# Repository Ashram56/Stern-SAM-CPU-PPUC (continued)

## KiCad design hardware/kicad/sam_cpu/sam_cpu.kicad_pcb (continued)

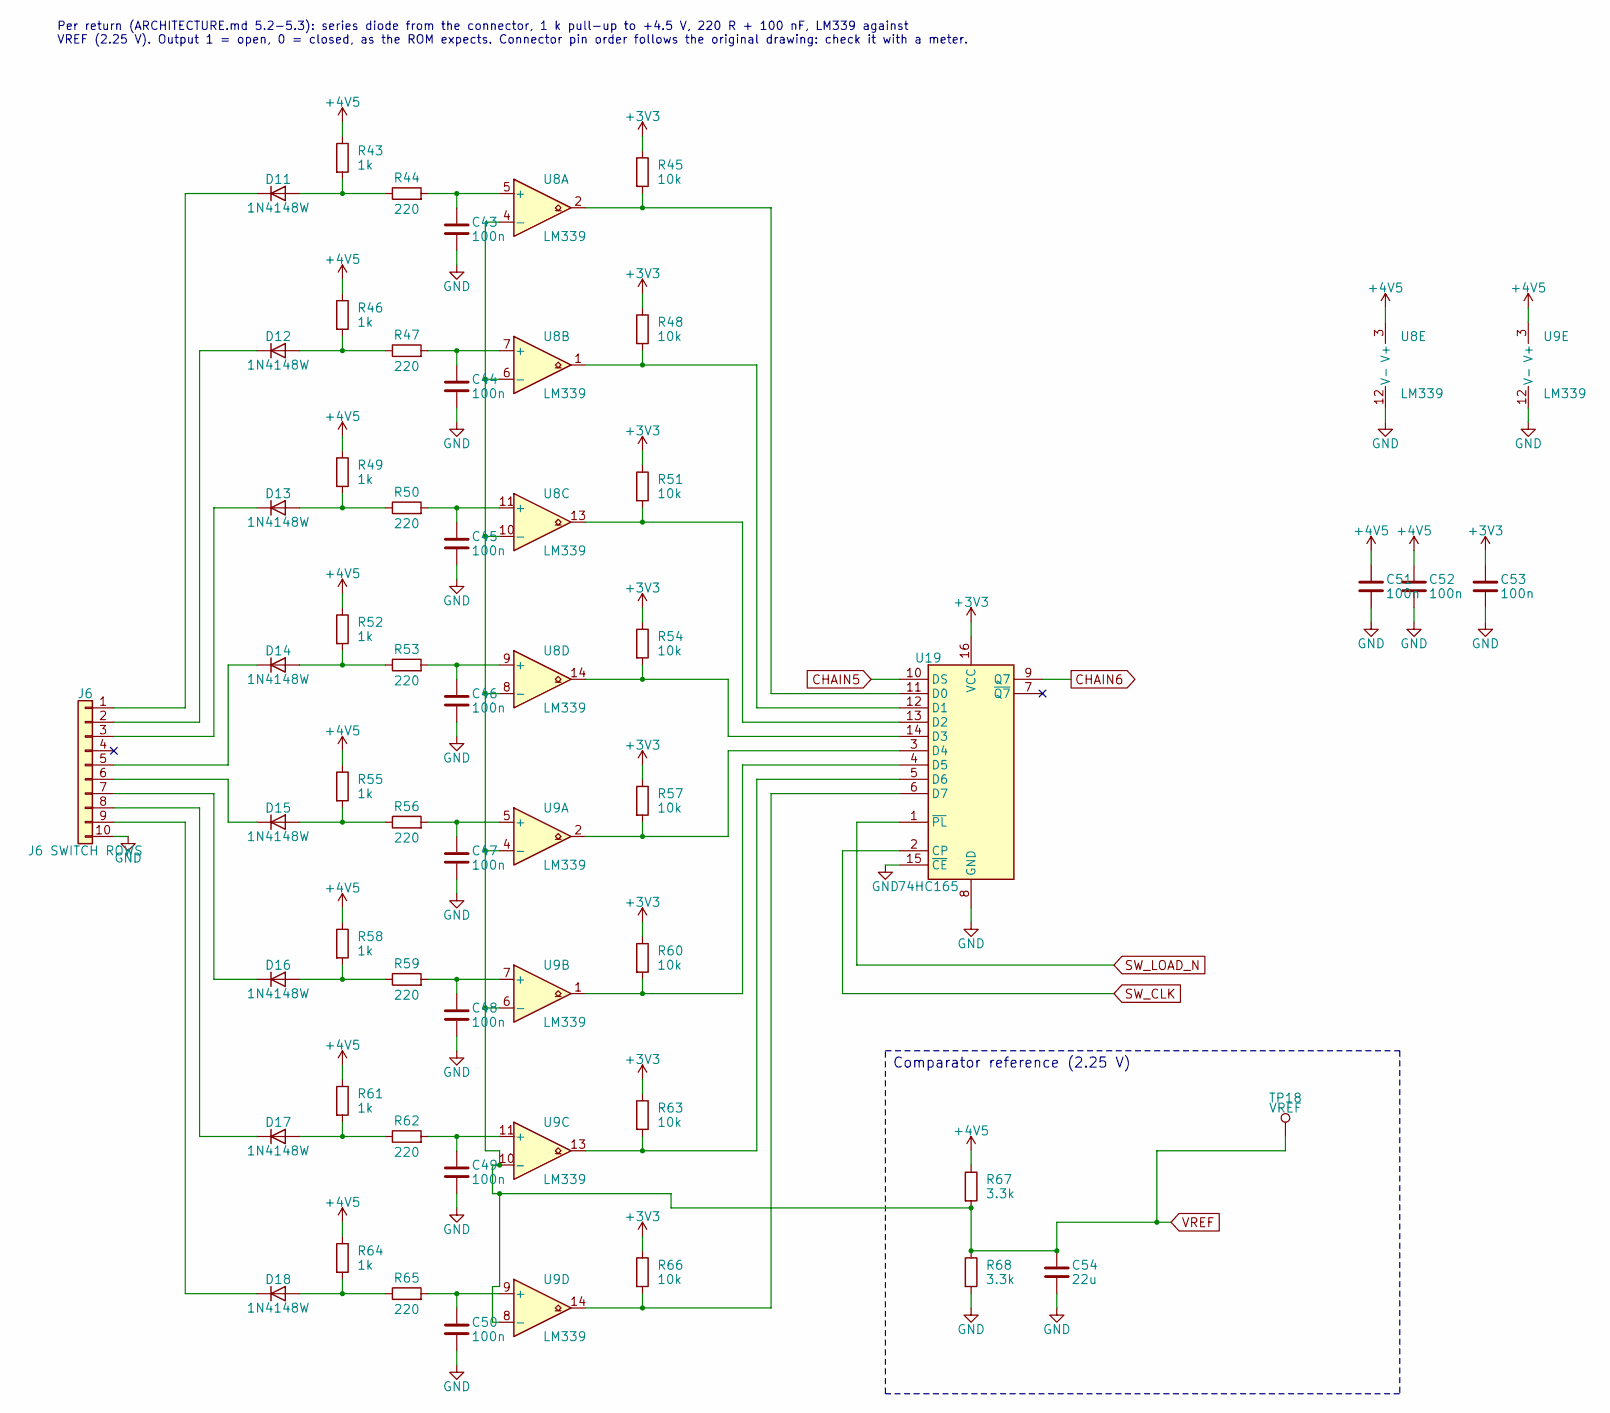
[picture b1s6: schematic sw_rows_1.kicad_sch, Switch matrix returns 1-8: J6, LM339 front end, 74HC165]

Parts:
C43, C44, C45, C46, C47, C48, C49, C50: 100n; C_0603_1608Metric
C51, C52, C53: 100n; C_0805_2012Metric
C54: 22u; C_0805_2012Metric
D11, D12, D13, D14, D15, D16, D17, D18: 1N4148W; D_SOD-123
J6: J6 SWITCH ROWS; Molex_KK-396_A-41791-0010_1x10_P3.96mm_Vertical
R43, R46, R49, R52, R55, R58, R61, R64: 1k; R_0603_1608Metric
R44, R50, R62, R65: 220; R_0805_2012Metric
R45, R51, R57, R60, R63: 10k; R_0603_1608Metric
R47, R53, R56, R59: 220; R_0603_1608Metric
R48, R54, R66: 10k; R_0805_2012Metric
R67: 3.3k; R_0603_1608Metric
R68: 3.3k; R_0805_2012Metric
TP18: VREF; TestPoint_Pad_D1.5mm
U8, U9: LM339; SOIC-14_3.9x8.7mm_P1.27mm
U19: 74HC165; SOIC-16_3.9x9.9mm_P1.27mm

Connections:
+3V3: C53.1, R45.1, R48.1, R51.1, R54.1, R57.1, R60.1, R63.1, R66.1, U19.16 (VCC); also elsewhere on the board
+4V5: C51.1, C52.1, R43.1, R46.1, R49.1, R52.1, R55.1, R58.1, R61.1, R64.1, R67.1, U8.3 (V+), U9.3 (V+); also elsewhere on the board
CHAIN5: U19.10 (DS); also elsewhere on the board
CHAIN6: U19.9 (Q7); also elsewhere on the board
GND: C43.2, C44.2, C45.2, C46.2, C47.2, C48.2, C49.2, C50.2, C51.2, C52.2, C53.2, C54.2, J6.10, R68.2, U8.12 (V-), U9.12 (V-), U19.8 (GND), U19.15 (~CE); also elsewhere on the board
unnamed: D11.2 (A), R43.2, R44.1
unnamed: D11.1 (K), J6.1
unnamed: D12.2 (A), R46.2, R47.1
unnamed: D12.1 (K), J6.2
unnamed: D13.2 (A), R49.2, R50.1
unnamed: D13.1 (K), J6.3
unnamed: D14.2 (A), R52.2, R53.1
unnamed: D14.1 (K), J6.5
unnamed: D15.2 (A), R55.2, R56.1
unnamed: D15.1 (K), J6.6
unnamed: D16.2 (A), R58.2, R59.1
unnamed: D16.1 (K), J6.7
unnamed: D17.2 (A), R61.2, R62.1
unnamed: D17.1 (K), J6.8
unnamed: D18.2 (A), R64.2, R65.1
unnamed: D18.1 (K), J6.9
unnamed: C43.1, R44.2, U8.5 (+)
unnamed: C44.1, R47.2, U8.7 (+)
unnamed: C45.1, R50.2, U8.11 (+)
unnamed: C46.1, R53.2, U8.9 (+)
unnamed: C47.1, R56.2, U9.5 (+)
unnamed: C48.1, R59.2, U9.7 (+)
unnamed: C49.1, R62.2, U9.11 (+)
unnamed: C50.1, R65.2, U9.9 (+)
unnamed: R45.2, U8.2, U19.11 (D0)
unnamed: R48.2, U8.1, U19.12 (D1)
unnamed: R51.2, U8.13, U19.13 (D2)
unnamed: R54.2, U8.14, U19.14 (D3)
unnamed: R57.2, U9.2, U19.3 (D4)
unnamed: R60.2, U9.1, U19.4 (D5)
unnamed: R63.2, U9.13, U19.5 (D6)
unnamed: R66.2, U9.14, U19.6 (D7)
SW_CLK: U19.2 (CP); also elsewhere on the board
SW_LOAD_N: U19.1 (~PL); also elsewhere on the board
VREF: C54.1, R67.2, R68.1, TP18.1, U8.4 (-), U8.6 (-), U8.8 (-), U8.10 (-), U9.4 (-), U9.6 (-), U9.8 (-), U9.10 (-); also elsewhere on the board

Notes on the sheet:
Comparator reference (2.25 V)
Per return (ARCHITECTURE.md 5.2-5.3): series diode from the connector, 1 k pull-up to +4.5 V, 220 R + 100 nF, LM339 against VREF (2.25 V). Output 1 = open, 0 = closed, as the ROM expects. Connector pin order follows the original drawing: check it with a meter.

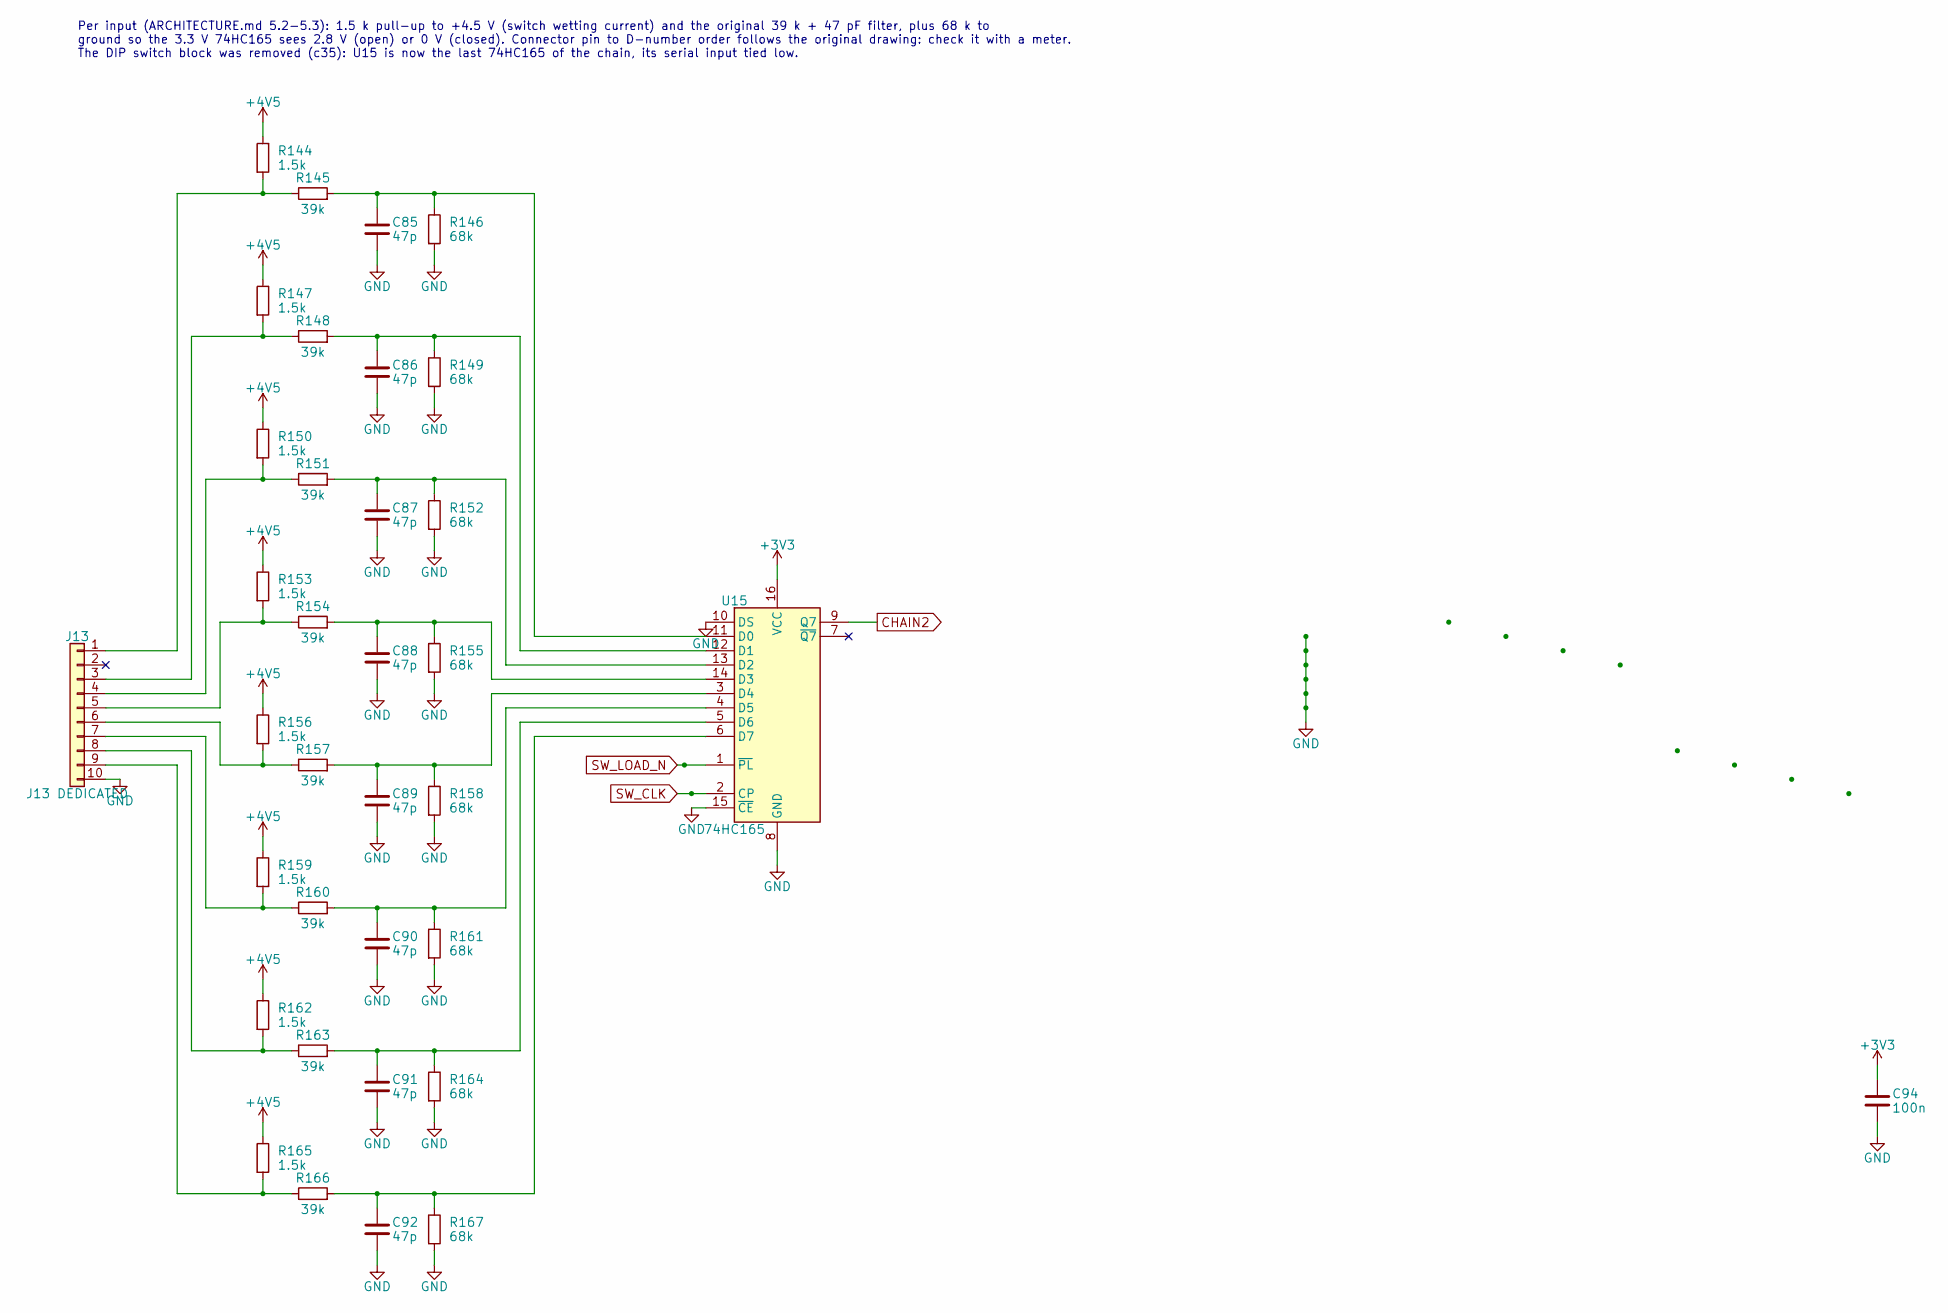
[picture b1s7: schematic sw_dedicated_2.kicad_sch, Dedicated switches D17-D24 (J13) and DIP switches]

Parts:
C85: 47p; C_0805_2012Metric
C86, C87, C88, C89, C90, C91, C92: 47p; C_0603_1608Metric
C94: 100n; C_0805_2012Metric
J13: J13 DEDICATED; Molex_KK-396_A-41791-0010_1x10_P3.96mm_Vertical
R144, R147, R150, R153, R156, R159, R165: 1.5k; R_0603_1608Metric
R145, R148, R151, R154, R157, R160, R163, R166: 39k; R_0603_1608Metric
R146, R149, R152, R161, R167: 68k; R_0603_1608Metric
R155, R158, R164: 68k; R_0805_2012Metric
R162: 1.5k; R_0805_2012Metric
U15: 74HC165; SOIC-16_3.9x9.9mm_P1.27mm

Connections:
+3V3: C94.1, U15.16 (VCC); also elsewhere on the board
+4V5: R144.1, R147.1, R150.1, R153.1, R156.1, R159.1, R162.1, R165.1; also elsewhere on the board
CHAIN2: U15.9 (Q7); also elsewhere on the board
GND: C85.2, C86.2, C87.2, C88.2, C89.2, C90.2, C91.2, C92.2, C94.2, J13.10, R146.2, R149.2, R152.2, R155.2, R158.2, R161.2, R164.2, R167.2, U15.8 (GND), U15.10 (DS), U15.15 (~CE); also elsewhere on the board
unnamed: J13.1, R144.2, R145.1
unnamed: J13.3, R147.2, R148.1
unnamed: J13.4, R150.2, R151.1
unnamed: J13.5, R153.2, R154.1
unnamed: J13.6, R156.2, R157.1
unnamed: J13.7, R159.2, R160.1
unnamed: J13.8, R162.2, R163.1
unnamed: J13.9, R165.2, R166.1
unnamed: C85.1, R145.2, R146.1, U15.11 (D0)
unnamed: C86.1, R148.2, R149.1, U15.12 (D1)
unnamed: C87.1, R151.2, R152.1, U15.13 (D2)
unnamed: C88.1, R154.2, R155.1, U15.14 (D3)
unnamed: C89.1, R157.2, R158.1, U15.3 (D4)
unnamed: C90.1, R160.2, R161.1, U15.4 (D5)
unnamed: C91.1, R163.2, R164.1, U15.5 (D6)
unnamed: C92.1, R166.2, R167.1, U15.6 (D7)
SW_CLK: U15.2 (CP); also elsewhere on the board
SW_LOAD_N: U15.1 (~PL); also elsewhere on the board

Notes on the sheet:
Per input (ARCHITECTURE.md 5.2-5.3): 1.5 k pull-up to +4.5 V (switch wetting current) and the original 39 k + 47 pF filter, plus 68 k to ground so the 3.3 V 74HC165 sees 2.8 V (open) or 0 V (closed). Connector pin to D-number order follows the original drawing: check it with a meter. The DIP switch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

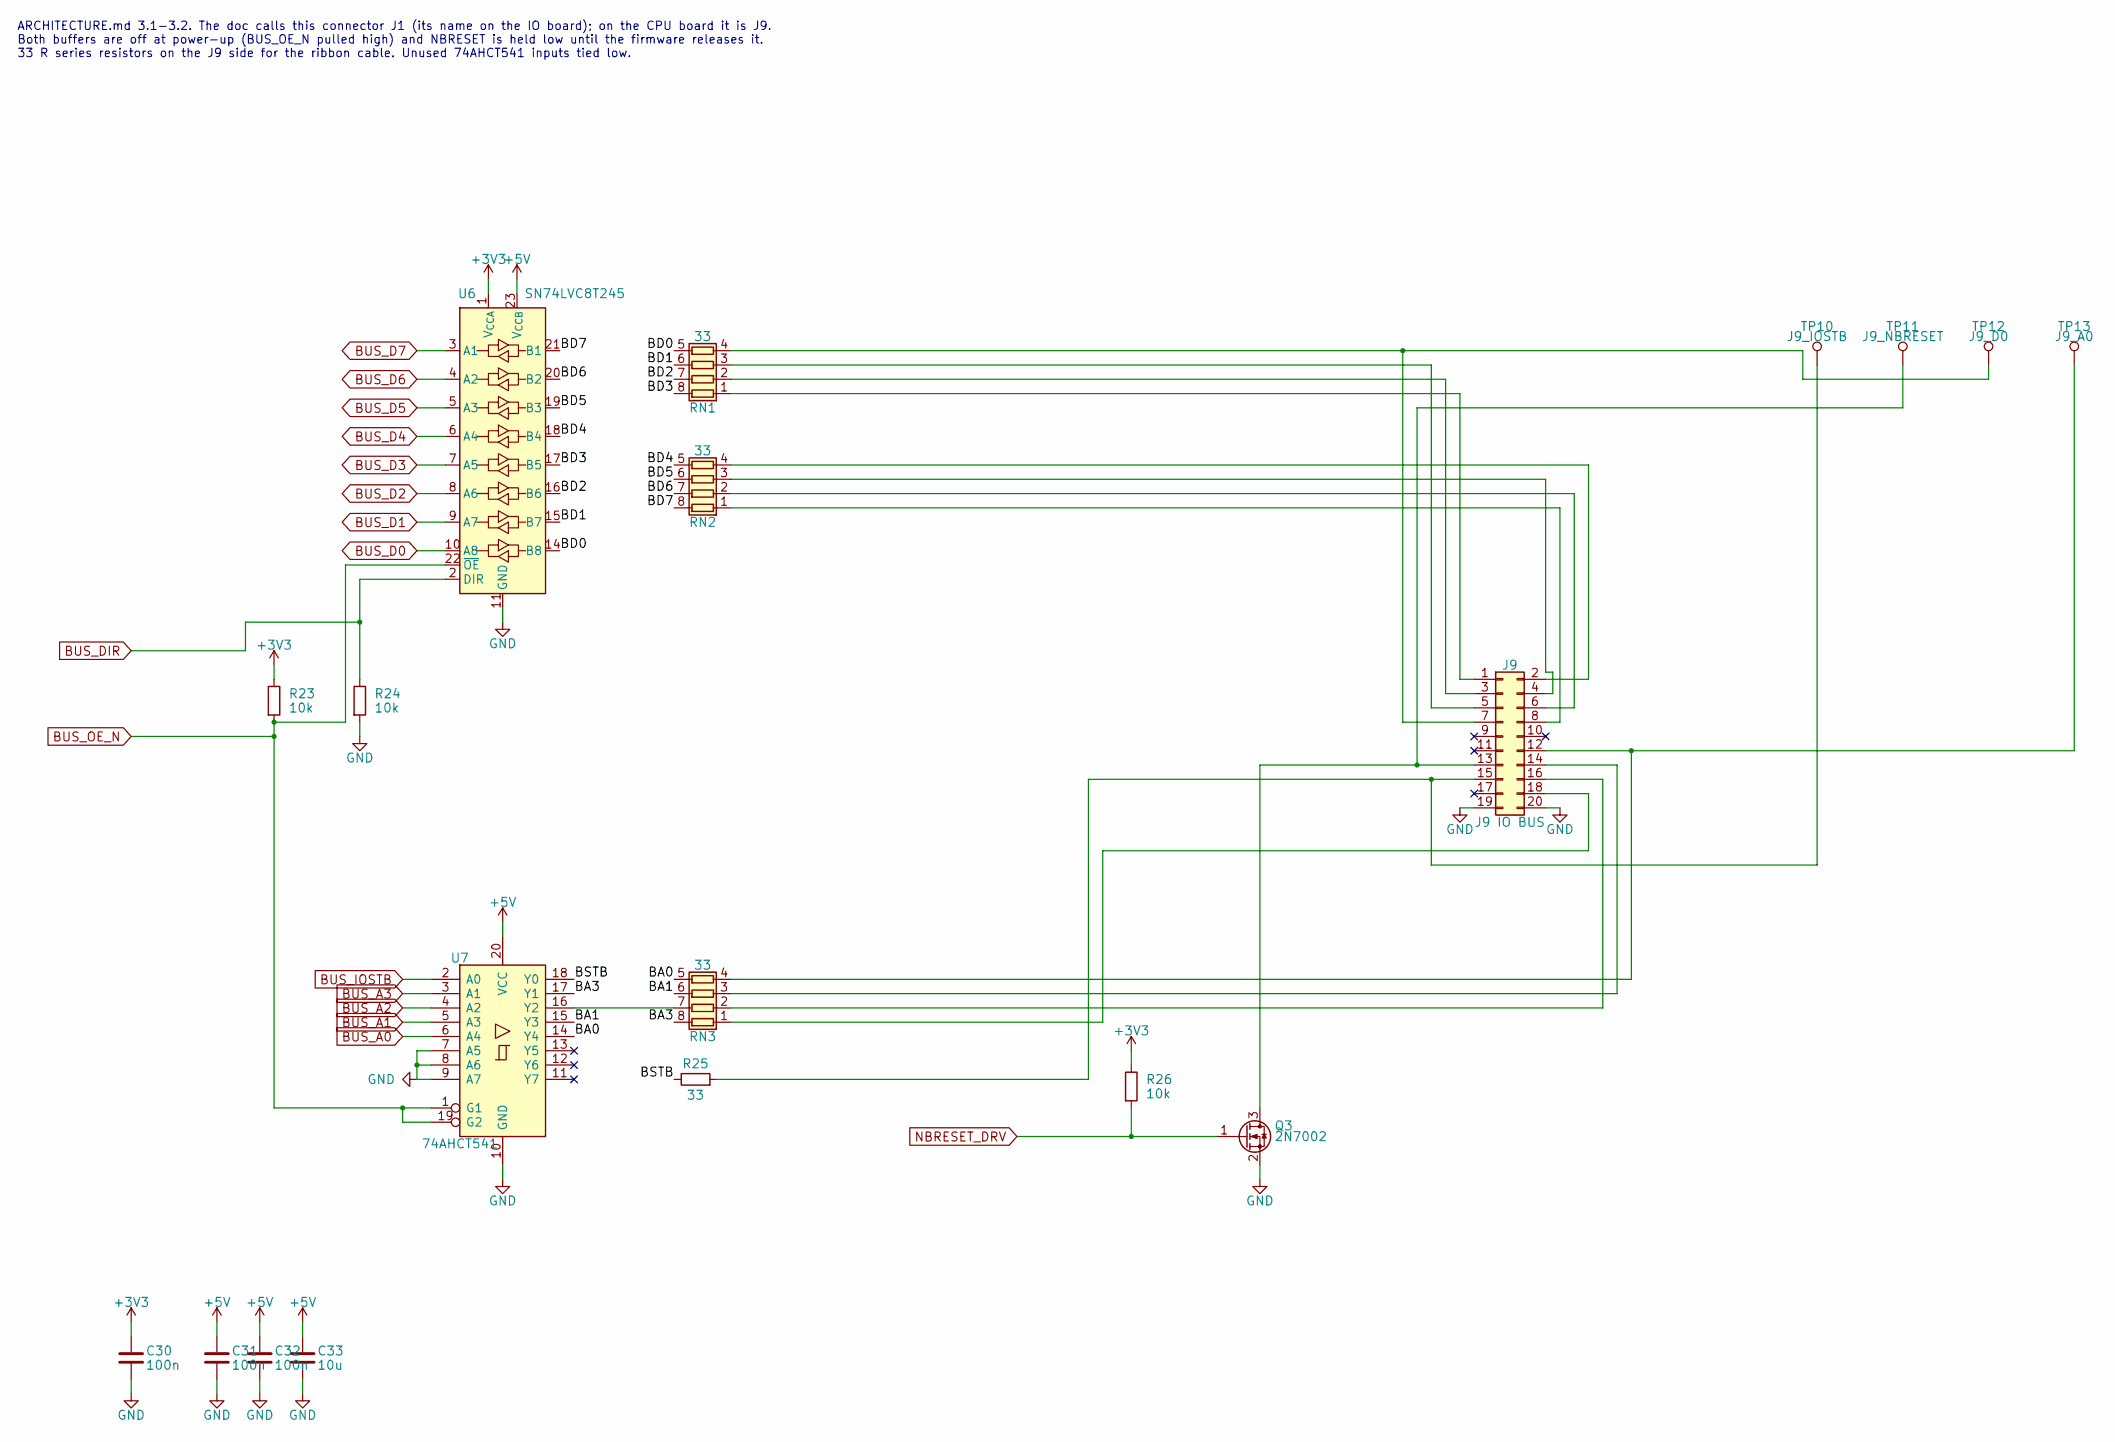
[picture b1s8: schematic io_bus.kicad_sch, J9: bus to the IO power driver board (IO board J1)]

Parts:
C30: 100n; C_0805_2012Metric
C31, C32: 100n; C_0603_1608Metric
C33: 10u; C_0805_2012Metric
J9: J9 IO BUS; IDC-Header_2x10_P2.54mm_Vertical
Q3: 2N7002; SOT-23
R23, R24, R26: 10k; R_0603_1608Metric
R25: 33; R_0603_1608Metric
RN1, RN2, RN3: 33; R_Array_Convex_4x0603
TP10: J9_IOSTB; TestPoint_Pad_D1.5mm
TP11: J9_NBRESET; TestPoint_Pad_D1.5mm
TP12: J9_D0; TestPoint_Pad_D1.5mm
TP13: J9_A0; TestPoint_Pad_D1.5mm
U6: SN74LVC8T245; TSSOP-24_4.4x7.8mm_P0.65mm
U7: 74AHCT541; TSSOP-20_4.4x6.5mm_P0.65mm

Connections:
+3V3: C30.1, R23.1, R26.1, U6.1 (V_{CCA}); also elsewhere on the board
+5V: C31.1, C32.1, C33.1, U6.23 (V_{CCB}), U6.24 (V_{CCB}), U7.20 (VCC); also elsewhere on the board
/IO bus/BA0: RN3.5 (R4.2), U7.14 (Y4)
/IO bus/BA1: RN3.6 (R3.2), U7.15 (Y3)
/IO bus/BA3: RN3.8 (R1.2), U7.17 (Y1)
/IO bus/BD0: RN1.5 (R4.2), U6.14 (B8)
/IO bus/BD1: RN1.6 (R3.2), U6.15 (B7)
/IO bus/BD2: RN1.7 (R2.2), U6.16 (B6)
/IO bus/BD3: RN1.8 (R1.2), U6.17 (B5)
/IO bus/BD4: RN2.5 (R4.2), U6.18 (B4)
/IO bus/BD5: RN2.6 (R3.2), U6.19 (B3)
/IO bus/BD6: RN2.7 (R2.2), U6.20 (B2)
/IO bus/BD7: RN2.8 (R1.2), U6.21 (B1)
/IO bus/BSTB: R25.1, U7.18 (Y0)
BUS_A0: U7.6 (A4); also elsewhere on the board
BUS_A1: U7.5 (A3); also elsewhere on the board
BUS_A2: U7.4 (A2); also elsewhere on the board
BUS_A3: U7.3 (A1); also elsewhere on the board
BUS_D0: U6.10 (A8); also elsewhere on the board
BUS_D1: U6.9 (A7); also elsewhere on the board
BUS_D2: U6.8 (A6); also elsewhere on the board
BUS_D3: U6.7 (A5); also elsewhere on the board
BUS_D4: U6.6 (A4); also elsewhere on the board
BUS_D5: U6.5 (A3); also elsewhere on the board
BUS_D6: U6.4 (A2); also elsewhere on the board
BUS_D7: U6.3 (A1); also elsewhere on the board
BUS_DIR: R24.1, U6.2 (DIR); also elsewhere on the board
BUS_IOSTB: U7.2 (A0); also elsewhere on the board
BUS_OE_N: R23.2, U6.22 (~OE), U7.1 (G1), U7.19 (G2); also elsewhere on the board
GND: C30.2, C31.2, C32.2, C33.2, J9.19, J9.20, Q3.2 (S), R24.2, U6.11 (GND), U6.12 (GND), U6.13 (GND), U7.7 (A5), U7.8 (A6), U7.9 (A7), U7.10 (GND); also elsewhere on the board
NBRESET_DRV: Q3.1 (G), R26.2; also elsewhere on the board
unnamed: J9.1, RN1.1 (R1.1)
unnamed: J9.2, RN2.4 (R4.1)
unnamed: J9.3, RN1.2 (R2.1)
unnamed: J9.4, RN2.3 (R3.1)
unnamed: J9.5, RN1.3 (R3.1)
unnamed: J9.6, RN2.2 (R2.1)
unnamed: J9.7, RN1.4 (R4.1), TP12.1
unnamed: J9.8, RN2.1 (R1.1)
unnamed: J9.12, RN3.4 (R4.1), TP13.1
unnamed: J9.13, Q3.3 (D), TP11.1
unnamed: J9.14, RN3.3 (R3.1)
unnamed: J9.15, R25.2, TP10.1
unnamed: J9.16, RN3.2 (R2.1)
unnamed: J9.18, RN3.1 (R1.1)
unnamed: RN3.7 (R2.2), U7.16 (Y2)

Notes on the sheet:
ARCHITECTURE.md 3.1-3.2. The doc calls this connector J1 (its name on the IO board); on the CPU board it is J9. Both buffers are off at power-up (BUS_OE_N pulled high) and NBRESET is held low until the firmware releases it. 33 R series resistors on the J9 side for the ribbon cable. Unused 74AHCT541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

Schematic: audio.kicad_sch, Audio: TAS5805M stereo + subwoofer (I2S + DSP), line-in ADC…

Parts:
C96, C98, C113, C115: 22u; C_1206_3216Metric
C97, C99, C101, C114, C116, C146, C148, C150, C152, C153, C159, C160: 100n; C_0805_2012Metric
C100, C117, C154, C156: 4.7u; C_0805_2012Metric
C102, C103, C120, C121: 1u; C_0805_2012Metric
C104, C106, C109, C111, C138, C140, C142, C144: 220n; C_0805_2012Metric
C105, C107, C110, C112, C139, C141, C143, C145: 680n; C_0805_2012Metric
C108, C118: 470u; CP_Elec_8x10
C147, C149, C151: 10u; C_0805_2012Metric
C155, C157: 470p; C_0805_2012Metric
C158: 100nF; C_0805_2012Metric
FB4: 600R; L_0805_2012Metric
J10: J10 SPEAKERS; Molex_KK-396_A-41791-0004_1x04_P3.96mm_Vertical
J22: J22 STEREO; Molex_KK-396_A-41791-0004_1x04_P3.96mm_Vertical
J24: J24 SUBWOOFER; Molex_KK-396_A-41791-0004_1x04_P3.96mm_Vertical
L3, L4, L5, L6, L7, L8, L9, L10: 10u; L_Changjiang_FXL0630
R186, R188, R189: 4.7k; R_0805_2012Metric
R187: 15k; R_0805_2012Metric
R190, R194, R195, R196, R197, R202: 10k; R_0805_2012Metric
R191, R192, R193: 33; R_0805_2012Metric
R198: 220k; R_0805_2012Metric
R199, R200, R201: 100k; R_0805_2012Metric
U22: PCM1808; TSSOP-14_4.4x5mm_P0.65mm
U23, U24: TAS5805M; TSSOP-28-1EP_4.4x9.7mm_P0.65mm_EP3.4x9.7mm_Mask3.1x4.05mm_T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
U26: 74HC157; SOIC-16_3.9x9.9mm_P1.27mm
Y2: 12.288MHz; Oscillator_SMD_Abracon_ASE-4Pin_3.2x2.5mm

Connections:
+3V3: C100.1, C101.1, C117.1, C146.1, C149.1, C150.1, C153.1, C159.1, R186.1, R187.1, R188.1, R189.1, R190.1, R198.1, U22.4 (VDD), U22.10 (MD0), U22.11 (MD1), U23.2 (DVDD), U24.2 (DVDD), U26.16 (VCC), Y2.1 (EN), Y2.4 (Vdd); also elsewhere on the board
+5V: FB4.1; also elsewhere on the board
+12V: C96.1, C97.1, C98.1, C99.1, C108.1, C113.1, C114.1, C115.1, C116.1, C118.1, U23.15 (PVDD), U23.16 (PVDD), U23.27 (PVDD), U23.28 (PVDD), U24.15 (PVDD), U24.16 (PVDD), U24.27 (PVDD), U24.28 (PVDD); also elsewhere on the board
/Audio/ADC_BCK: U22.8 (BCK), U26.6 (I1b)
/Audio/ADC_DOUT: U22.9 (DOUT), U26.10 (I1c)
/Audio/ADC_INL: C154.2, U22.13 (VINL)
/Audio/ADC_INR: C156.2, U22.14 (VINR)
/Audio/ADC_LRCK: U22.7 (LRCK), U26.3 (I1a)
/Audio/ADC_SCKI: U22.6 (SCKI), Y2.3 (OUT)
/Audio/ADC_VCC: C147.1, C148.1, FB4.2, U22.3 (VCC)
/Audio/ADC_VREF: C151.1, C152.1, U22.1 (VREF)
/Audio/AMP1_ADR: R186.2, U23.3 (ADR/~FAULT)
/Audio/AMP1_AVDD: C102.1, U23.13 (AVDD)
/Audio/AMP1_BSTA_N: C106.1, U23.22 (BST_A-)
/Audio/AMP1_BSTA_P: C104.1, U23.25 (BST_A+)
/Audio/AMP1_BSTB_N: C111.1, U23.21 (BST_B-)
/Audio/AMP1_BSTB_P: C109.1, U23.18 (BST_B+)
/Audio/AMP1_OUTA_N: C106.2, L4.1, U23.23 (OUT_A-)
/Audio/AMP1_OUTA_P: C104.2, L3.1, U23.26 (OUT_A+)
/Audio/AMP1_OUTB_N: C111.2, L6.1, U23.20 (OUT_B-)
/Audio/AMP1_OUTB_P: C109.2, L5.1, U23.17 (OUT_B+)
/Audio/AMP1_VRDIG: C103.1, U23.4 (VR_DIG)
/Audio/AMP2_ADR: R187.2, U24.3 (ADR/~FAULT)
/Audio/AMP2_AVDD: C120.1, U24.13 (AVDD)
/Audio/AMP2_BSTA_N: C140.1, U24.22 (BST_A-)
/Audio/AMP2_BSTA_P: C138.1, U24.25 (BST_A+)
/Audio/AMP2_BSTB_N: C144.1, U24.21 (BST_B-)
/Audio/AMP2_BSTB_P: C142.1, U24.18 (BST_B+)
/Audio/AMP2_OUTA_N: C140.2, L8.1, U24.23 (OUT_A-)
/Audio/AMP2_OUTA_P: C138.2, L7.1, U24.26 (OUT_A+)
/Audio/AMP2_OUTB_N: C144.2, L10.1, U24.20 (OUT_B-)
/Audio/AMP2_OUTB_P: C142.2, L9.1, U24.17 (OUT_B+)
/Audio/AMP2_VRDIG: C121.1, U24.4 (VR_DIG)
/Audio/AMP_LRCLK: R192.2, U23.6 (LRCLK), U24.6 (LRCLK)
/Audio/AMP_SCLK: R191.2, U23.7 (SCLK), U24.7 (SCLK)
/Audio/AMP_SDIN: R193.2, U23.8 (SDIN), U24.8 (SDIN)
/Audio/LIN_L_DIV: C154.1, C155.1, R194.2, R195.1
/Audio/LIN_R_DIV: C156.1, C157.1, R196.2, R197.1
/Audio/MUX_BCK: R191.1, U26.7 (Zb)
/Audio/MUX_DIN: R193.1, U26.9 (Zc)
/Audio/MUX_LRCK: R192.1, U26.4 (Za)
/Audio/MUX_SEL: C160.1, R202.2, U26.1 (S)
/Audio/SPK_L_N: C107.1, J10.3, J22.2, L4.2
/Audio/SPK_L_P: C105.1, J10.1, J22.1, L3.2
/Audio/SPK_R_N: C112.1, J10.4, J22.4, L6.2
/Audio/SPK_R_P: C110.1, J10.2, J22.3, L5.2
/Audio/SUB1_N: C141.1, J24.2, L8.2
/Audio/SUB1_P: C139.1, J24.1, L7.2
/Audio/SUB2_N: C145.1, J24.4, L10.2
/Audio/SUB2_P: C143.1, J24.3, L9.2
AMP_PDN: C158.1, R190.2, U23.12 (~PDN), U24.12 (~PDN); also elsewhere on the board
AMP_SCL: R189.2, U23.11 (SCL), U24.11 (SCL); also elsewhere on the board
AMP_SDA: R188.2, U23.10 (SDA), U24.10 (SDA); also elsewhere on the board
GND: C96.2, C97.2, C98.2, C99.2, C100.2, C101.2, C102.2, C103.2, C105.2, C107.2, C108.2, C110.2, C112.2, C113.2, C114.2, C115.2, C116.2, C117.2, C118.2, C120.2, C121.2, C139.2, C141.2, C143.2, C145.2, C146.2, C147.2, C148.2, C149.2, C150.2, C151.2, C152.2, C153.2, C155.2, C157.2, C158.2, C159.2, C160.2, R195.2, R197.2, R199.2, R200.2, R201.2, U22.2 (AGND), U22.5 (DGND), U22.12 (FMT), U23.1 (DGND), U23.5 (DGND), U23.14 (AGND), U23.19 (PGND), U23.24 (PGND), U23.29 (EP), U24.1 (DGND), U24.5 (DGND), U24.14 (AGND), U24.19 (PGND), U24.24 (PGND), U24.29 (EP), U26.8 (GND), U26.13 (I1d), U26.14 (I0d), U26.15 (E), Y2.2 (GND); also elsewhere on the board
I2S_BCK: R199.1, U26.5 (I0b); also elsewhere on the board
I2S_DIN: R201.1, U26.11 (I0c); also elsewhere on the board
I2S_LRCK: R200.1, U26.2 (I0a); also elsewhere on the board
LINEIN_L: R194.1; also elsewhere on the board
LINEIN_R: R196.1; also elsewhere on the board
LINE_DET: R198.2, R202.1; also elsewhere on the board

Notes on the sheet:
Stereo amplifier: left = OUT_A, right = OUT_B (bridged) (U23, I2C address 0x2C (ADR 4.7k))
PVDD (+12V): bulk + 22 uF + 100 nF at each PVDD pin pair
DVDD (+3V3), AVDD, VR_DIG
ADR: I2C address 0x2C (ADR 4.7k)
Bootstrap 220 nF, LC filter 10 uH + 680 nF (4 or 8 ohm), switching 768 kHz (or BD 384 kHz)
Original connector: pins 3 / 4 = minus
Same channels as pairs
Subwoofer amplifier: both channels carry the DSP subwoofer mix (U24, I2C address 0x2D (ADR 15k))
ADR: I2C address 0x2D (ADR 15k)
Dual voice coil or two subwoofers
Amplifier control: RP2354B I2C1 (GPIO38 SDA / GPIO39 SCL), PDN (GPIO35 + RC)
AMP_PDN rises 1 ms after +3V3 (10k / 100 nF) while GPIO35 is an input. GPIO35 low = hard reset / shutdown; the RP2354B also resets over I2C (0x01), keeps them in deep sleep until configured, then loads the PPC3 configuration over I2C (mode, 768 kHz switching, crossover, limiter): no sound without f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
I2S source: Pi / J28 when J30 is empty, line-in ADC when a plug is in
S low (A inputs): Pi. S high: ADC. 33 R series at the outputs.
Line-in ADC: PCM1808 master 256 fs (12.288 MHz -> 48 kHz, BCK 64 fs), I2S
Divider 10k / 10k: 2 Vrms in -> 0.92 Vrms (full scale 1.06 Vrms). J30 TN = LINE_DET: low through 20k without a plug, high (220k) with a plug.
Digital audio chain: I2S (Pi on J21 / J28, or the PCM1808 line-in ADC) -> 74HC157 source select -> two TAS5805M with DSP (EQ, subwoofer crossover, limiter), +12 V, no heatsink. TAS5805M speaker outputs are bridged: no speaker wire may go to ground.
Without a Pi: 100k pull-downs on the I2S inputs; LINE_DET through 10k / 100 nF (1 ms, ESD)

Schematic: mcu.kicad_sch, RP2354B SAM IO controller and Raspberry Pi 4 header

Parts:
BT1: CR2032; BatteryHolder_Lianxin_XDCR-2032-603
C11, C12, C24: 4.7u; C_0805_2012Metric
C13, C17, C19, C20, C21, C22, C23, C119: 100n; C_0805_2012Metric
C14, C15, C16, C18, C25, C26, C27: 100n; C_0603_1608Metric
C28, C29: 15p; C_0603_1608Metric
D3: yellow; LED_0603_1608Metric
J19: USB-C (to Pi); USB_C_Receptacle_SH_U262-161N-4BVC11
J21: Raspberry Pi 40-pin; PinSocket_2x20_P2.54mm_Vertical
L1: 3.3u; L_Cenker_CKCS201610; MPN Abracon AOTA-B201610S3R3-101-T (polarit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
R8, R18, R19: 33; R_0805_2012Metric
R9, R22, R217: 10k; R_0805_2012Metric
R10: 100k; R_0805_2012Metric
R11: 5.1k; R_0603_1608Metric
R12: 5.1k; R_0805_2012Metric
R13: 27; R_0805_2012Metric
R14: 27; R_0603_1608Metric
R15: 1k; R_0805_2012Metric
R16, R17, R20: 1k; R_0603_1608Metric
SW1: RESET; SW_SPST_TL3342
SW2: BOOTSEL; SW_SPST_TL3342
TP7: +1V1; TestPoint_Pad_D1.5mm
TP8: RUN; TestPoint_Pad_D1.5mm
TP9: GND; TestPoint_Pad_D1.5mm
U4: RP2354B; QFN-80-1EP_10x10mm_P0.4mm_EP3.4x3.4mm
U5: TPS3808G33; SOT-23-6
U25: DS3231MZ; SOIC-8_3.9x4.9mm_P1.27mm
Y1: 12MHz; Crystal_SMD_3225-4Pin_3.2x2.5mm; MPN Abracon ABM8-272-T3

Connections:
+1V1: C24.1, C25.1, C26.1, C27.1, L1.2, TP7.1, U4.10 (DVDD), U4.32 (DVDD), U4.51 (DVDD), U4.65 (VREG_FB)
+3V3: C12.1, C13.1, C14.1, C15.1, C16.1, C17.1, C18.1, C19.1, C20.1, C21.1, C22.1, C23.1, C119.1, R8.1, R9.1, R22.1, R217.1, U4.5 (IOVDD), U4.15 (IOVDD), U4.24 (IOVDD), U4.29 (IOVDD), U4.41 (IOVDD), U4.50 (IOVDD), U4.59 (ADC_AVDD), U4.60 (IOVDD), U4.64 (VREG_VIN), U4.68 (USB_OTP_VDD), U4.69 (QSPI_IOVDD), U4.76 (IOVDD), U5.5 (SENSE), U5.6 (VDD), U25.2 (VCC); also elsewhere on the board
/MCU and Pi/BOOTSEL: R15.2, U4.75 (~QSPI_SS)
/MCU and Pi/MR_N: R20.2, R217.2, SW1.1, U5.3 (~MR)
/MCU and Pi/PI_3V3: J21.1 (3V3), J21.17 (3V3)
/MCU and Pi/PI_SCL: J21.5 (SCL/GPIO3), U25.8 (SCL)
/MCU and Pi/PI_SDA: J21.3 (SDA/GPIO2), U25.7 (SDA)
/MCU and Pi/SWCLK: J21.22 (GPIO25), U4.33 (SWCLK)
/MCU and Pi/SWDIO: J21.18 (GPIO24), U4.34 (SWDIO)
/MCU and Pi/USB_C_D+: J19.A6 (D+), J19.B6 (D+), R14.1
/MCU and Pi/USB_C_D-: J19.A7 (D-), J19.B7 (D-), R13.1
/MCU and Pi/USB_D+: R14.2, U4.67 (USB_DP)
/MCU and Pi/USB_D-: R13.2, U4.66 (USB_DM)
AMP_PDN: U4.44 (GPIO35); also elsewhere on the board
AMP_SCL: U4.48 (GPIO39); also elsewhere on the board
AMP_SDA: U4.47 (GPIO38); also elsewhere on the board
BUS_A0: U4.6 (GPIO8); also elsewhere on the board
BUS_A1: U4.7 (GPIO9); also elsewhere on the board
BUS_A2: U4.8 (GPIO10); also elsewhere on the board
BUS_A3: U4.9 (GPIO11); also elsewhere on the board
BUS_D0: U4.77 (GPIO0); also elsewhere on the board
BUS_D1: U4.78 (GPIO1); also elsewhere on the board
BUS_D2: U4.79 (GPIO2); also elsewhere on the board
BUS_D3: U4.80 (GPIO3); also elsewhere on the board
BUS_D4: U4.1 (GPIO4); also elsewhere on the board
BUS_D5: U4.2 (GPIO5); also elsewhere on the board
BUS_D6: U4.3 (GPIO6); also elsewhere on the board
BUS_D7: U4.4 (GPIO7); also elsewhere on the board
BUS_DIR: U4.12 (GPIO13); also elsewhere on the board
BUS_IOSTB: U4.11 (GPIO12); also elsewhere on the board
BUS_OE_N: U4.14 (GPIO15); also elsewhere on the board
FRAME_CS_N: J21.24 (~CE0/GPIO8), U4.52 (GPIO41/ADC1)
FRAME_MOSI: J21.19 (MOSI0/GPIO10), U4.49 (GPIO40/ADC0)
FRAME_SCK: J21.23 (SCLK0/GPIO11), U4.53 (GPIO42/ADC2)
GND: BT1.2 (-), C11.2, C12.2, C13.2, C14.2, C15.2, C16.2, C17.2, C18.2, C19.2, C20.2, C21.2, C22.2, C23.2, C24.2, C25.2, C26.2, C27.2, C28.2, C29.2, C119.2, D3.1 (K), J19.A1 (GND), J19.A12 (GND), J19.B1 (GND), J19.B12 (GND), J19.SH (SHIELD), J21.6 (GND), J21.9 (GND), J21.14 (GND), J21.20 (GND), J21.25 (GND), J21.30 (GND), J21.34 (GND), J21.39 (GND), R10.2, R11.2, R12.2, SW1.2, SW2.2, TP9.1, U4.62 (VREG_PGND), U4.81 (GND), U5.2 (GND), U25.5 (GND), Y1.2 (G), Y1.4 (G); also elsewhere on the board
I2S_BCK: J21.12 (GPIO18/PWM0); also elsewhere on the board
I2S_DIN: J21.40 (GPIO21/SCLK1); also elsewhere on the board
I2S_LRCK: J21.35 (GPIO19/MISO1); also elsewhere on the board
LED_STATUS: R17.2; also elsewhere on the board
NBRESET_DRV: U4.13 (GPIO14); also elsewhere on the board
unnamed: BT1.1 (+), U25.6 (VBAT)
unnamed: C29.1, R16.1, Y1.3
unnamed: D3.2 (A), R17.1
unnamed: J19.A5 (CC1), R11.1
unnamed: J19.B5 (CC2), R12.1
unnamed: J19.A4 (VBUS), J19.A9 (VBUS), J19.B4 (VBUS), J19.B9 (VBUS), R10.1
unnamed: J21.8 (GPIO14/TXD), R18.1
unnamed: J21.10 (GPIO15/RXD), R19.1
unnamed: J21.15 (GPIO22), R20.1
unnamed: R15.1, SW2.1
unnamed: R9.2, TP8.1, U4.35 (RUN), U5.1 (~RESET)
unnamed: C11.1, R8.2, U4.61 (VREG_AVDD)
unnamed: L1.1, U4.63 (VREG_LX)
unnamed: C28.1, U4.30 (XIN), Y1.1
unnamed: R16.2, U4.31 (XOUT)
PI_5V: J21.2 (5V), J21.4 (5V); also elsewhere on the board
PI_RS485_DE: J21.26 (~CE1/GPIO7); also elsewhere on the board
PI_RS485_RX: J21.29 (GCLK1/GPIO5); also elsewhere on the board
PI_RS485_TX: J21.7 (GCLK0/GPIO4); also elsewhere on the board
RP_IRQ_N: J21.16 (GPIO23), R22.2, U4.46 (GPIO37)
RP_RS485_DE: U4.22 (GPIO22); also elsewhere on the board
RP_RS485_RX: U4.21 (GPIO21); also elsewhere on the board
RP_RS485_TX: U4.20 (GPIO20); also elsewhere on the board
RP_UART_RX: R18.2, U4.56 (GPIO45/ADC5)
RP_UART_TX: R19.2, U4.55 (GPIO44/ADC4)
STB_DATA: U4.19 (GPIO19); also elsewhere on the board
SW_CLK: U4.16 (GPIO16); also elsewhere on the board
SW_DATA: U4.18 (GPIO18); also elsewhere on the board
SW_LOAD_N: U4.17 (GPIO17); also elsewhere on the board
VMON_5V: U4.57 (GPIO46/ADC6); also elsewhere on the board
VMON_12V: U4.58 (GPIO47/ADC7); also elsewhere on the board

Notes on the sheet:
Test points
Raspberry Pi 4 (40-pin header J21)
GPIO map: ARCHITECTURE.md 9.2. PIO0 bus on GPIO0-15, PIO1 switch chain on GPIO16-20, GPIO20-22: RS485 port (UART1 TX / RX, driver enable, page 13); GPIO23-36 unassigned. Pi UART3 (GPIO4 / 5, RTS on GPIO7) reaches the same port. Frames from the Pi on SPI1 (GPIO40-42), UART0 on GPIO44-45, ADC monitor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
Real-time clock (Pi I2C1, CR2032 backup)

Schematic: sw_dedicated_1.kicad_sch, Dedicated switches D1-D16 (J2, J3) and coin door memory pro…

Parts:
C66, C69, C70, C71, C72, C73, C75, C77, C78, C79, C80, C81, C82, C83: 47p; C_0603_1608Metric
C67, C68, C76: 47p; C_0805_2012Metric
C74, C84: 100n; C_0805_2012Metric
J2: J2 DEDICATED; Molex_KK-396_A-41791-0012_1x12_P3.96mm_Vertical
J3: J3 DEDICATED; Molex_KK-396_A-41791-0010_1x10_P3.96mm_Vertical
R93, R99, R102, R105, R108, R111, R114, R120, R123, R126, R129, R132, R135, R138, R141: 1.5k; R_0603_1608Metric
R94, R100, R103, R106, R109, R112, R115, R127, R130, R136, R142: 39k; R_0603_1608Metric
R95, R98, R104, R110, R113, R119, R134: 68k; R_0805_2012Metric
R96: 1.5k; R_0805_2012Metric
R97, R118, R121, R124, R133, R139: 39k; R_0805_2012Metric
R101, R107, R116, R122, R125, R128, R131, R137, R140, R143: 68k; R_0603_1608Metric
R117: 4.7k; R_0603_1608Metric
U16, U17: 74HC165; SOIC-16_3.9x9.9mm_P1.27mm

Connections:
+3V3: C74.1, C84.1, U16.16 (VCC), U17.16 (VCC); also elsewhere on the board
+4V5: R93.1, R96.1, R99.1, R102.1, R105.1, R108.1, R111.1, R114.1, R117.1, R120.1, R123.1, R126.1, R129.1, R132.1, R135.1, R138.1, R141.1; also elsewhere on the board
CHAIN2: U16.10 (DS); also elsewhere on the board
CHAIN4: U17.9 (Q7); also elsewhere on the board
GND: C66.2, C67.2, C68.2, C69.2, C70.2, C71.2, C72.2, C73.2, C74.2, C75.2, C76.2, C77.2, C78.2, C79.2, C80.2, C81.2, C82.2, C83.2, C84.2, J2.11, J2.12, J3.10, R95.2, R98.2, R101.2, R104.2, R107.2, R110.2, R113.2, R116.2, R119.2, R122.2, R125.2, R128.2, R131.2, R134.2, R137.2, R140.2, R143.2, U16.8 (GND), U16.15 (~CE), U17.8 (GND), U17.15 (~CE); also elsewhere on the board
MEM_PROTECT: C75.1, R118.2, R119.1; also elsewhere on the board
unnamed: J2.1, R93.2, R94.1
unnamed: J2.2, R96.2, R97.1
unnamed: J2.3, R99.2, R100.1
unnamed: J2.4, R102.2, R103.1
unnamed: J2.6, R105.2, R106.1
unnamed: J2.7, R108.2, R109.1
unnamed: J2.8, R111.2, R112.1
unnamed: J2.9, R114.2, R115.1
unnamed: J2.10, R117.2, R118.1
unnamed: J3.1, R120.2, R121.1
unnamed: J3.2, R123.2, R124.1
unnamed: J3.4, R126.2, R127.1
unnamed: J3.5, R129.2, R130.1
unnamed: J3.6, R132.2, R133.1
unnamed: J3.7, R135.2, R136.1
unnamed: J3.8, R138.2, R139.1
unnamed: J3.9, R141.2, R142.1
unnamed: C76.1, R121.2, R122.1, U16.11 (D0)
unnamed: C77.1, R124.2, R125.1, U16.12 (D1)
unnamed: C78.1, R127.2, R128.1, U16.13 (D2)
unnamed: C79.1, R130.2, R131.1, U16.14 (D3)
unnamed: C80.1, R133.2, R134.1, U16.3 (D4)
unnamed: C81.1, R136.2, R137.1, U16.4 (D5)
unnamed: C82.1, R139.2, R140.1, U16.5 (D6)
unnamed: C83.1, R142.2, R143.1, U16.6 (D7)
unnamed: U16.9 (Q7), U17.10 (DS)
unnamed: C66.1, R94.2, R95.1, U17.11 (D0)
unnamed: C67.1, R97.2, R98.1, U17.12 (D1)
unnamed: C68.1, R100.2, R101.1, U17.13 (D2)
unnamed: C69.1, R103.2, R104.1, U17.14 (D3)
unnamed: C70.1, R106.2, R107.1, U17.3 (D4)
unnamed: C71.1, R109.2, R110.1, U17.4 (D5)
unnamed: C72.1, R112.2, R113.1, U17.5 (D6)
unnamed: C73.1, R115.2, R116.1, U17.6 (D7)
SW_CLK: U16.2 (CP), U17.2 (CP); also elsewhere on the board
SW_LOAD_N: U16.1 (~PL), U17.1 (~PL); also elsewhere on the board

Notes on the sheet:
Per input (ARCHITECTURE.md 5.2-5.3): 1.5 k pull-up to +4.5 V (switch wetting current) and the original 39 k + 47 pF filter, plus 68 k to ground so the 3.3 V 74HC165 sees 2.8 V (open) or 0 V (closed). Connector pin to D-number order follows the original drawing: check it with a meter. Memory protect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
